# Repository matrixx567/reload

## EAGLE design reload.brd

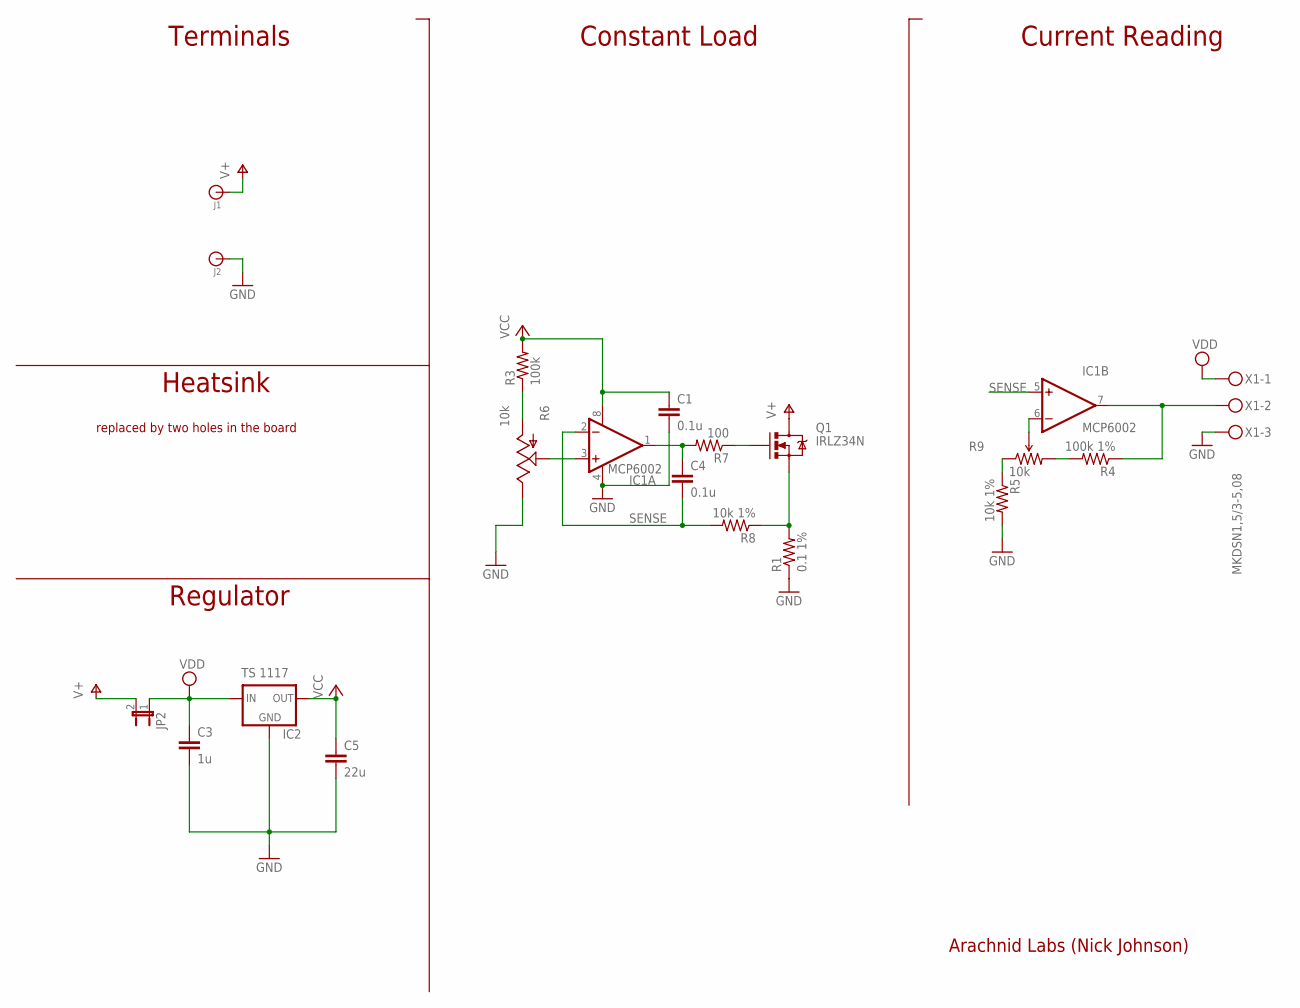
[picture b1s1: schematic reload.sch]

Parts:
C1, C4: 0.1u; 0805
C3: 1u; 0805
C5: 22u; 0805
IC1: MCP6002; SOP08
IC2: TS 1117; SOT223
J1, J2: BANANA_CONN
JP2: JUMPER-2PTH; 1X02
Q1: IRLZ34N; TO220V
R1: 0.1 1%; R2512
R3: 100k; 0805
R4: 100k 1%; 0805
R5, R8: 10k 1%; 0805
R6: 10k; ALPS_POT
R7: 100; 0805
R9: 10k; TRIMPOT-5MM
X1: MKDSN1,5/3-5,08

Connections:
GND: C1.2, C3.2, C5.2, IC1.4 (V-), IC2.2 (GND), J2.P$1, R1.1, R5.2, R6.P$1 (E), X1.3
IREF: IC1.7 (OUT), R4.1, X1.2
unnamed: C4.1, IC1.1 (OUT), R7.2
unnamed: R3.1, R6.P$3 (A)
unnamed: Q1.3 (S), R1.2, R8.1
unnamed: IC1.3 (+IN), R6.P$2 (S)
unnamed: IC1.6 (-IN), R9.B (WIPER)
unnamed: R5.1, R9.A (CCW)
unnamed: R4.2, R9.C (CW)
unnamed: Q1.1 (G), R7.1
SENSE: C4.2, IC1.2 (-IN), IC1.5 (+IN), R8.2
V+: J1.P$1, JP2.2, Q1.2 (D)
VCC: C1.1, C5.1, IC1.8 (V+), IC2.3 (OUT), R3.2
VDD: C3.1, IC2.1 (IN), JP2.1, X1.1

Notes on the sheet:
Terminals
Heatsink
Regulator
Constant Load
Current Reading
Arachnid Labs (Nick Johnson)
replaced by two holes in the board

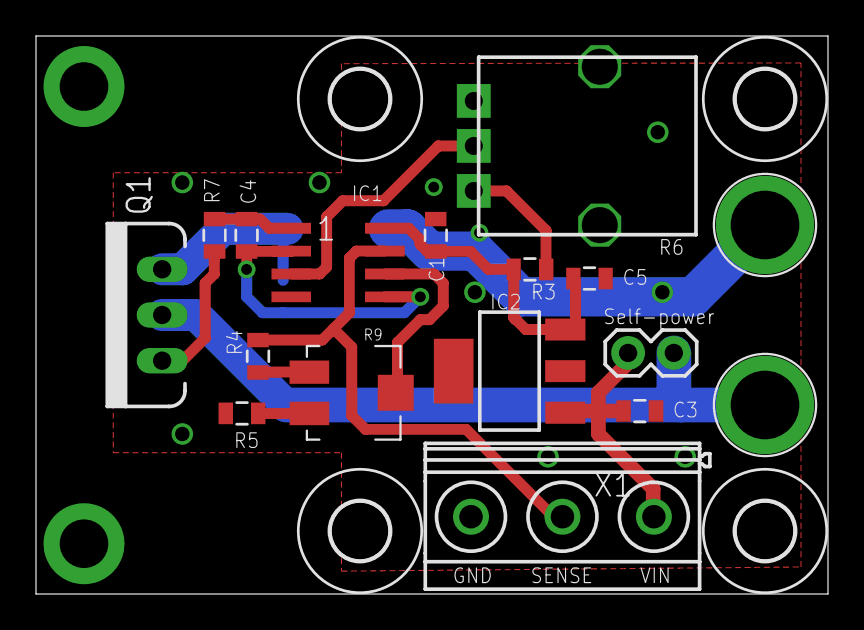
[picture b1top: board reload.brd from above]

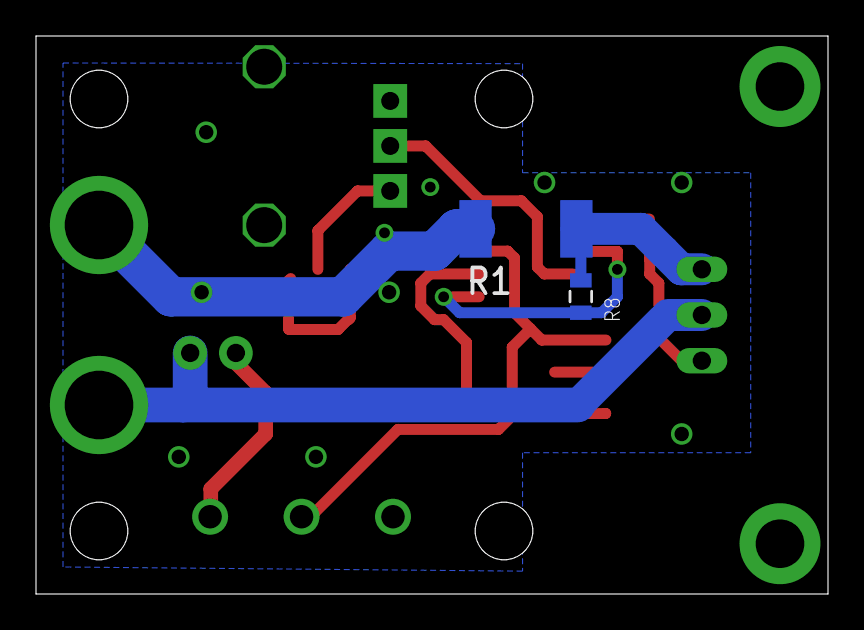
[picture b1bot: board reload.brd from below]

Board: 2 copper layers, 44.0 x 31.0 mm, 23 parts (2 on the bottom side), 14 nets.

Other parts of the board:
U$1, U$2, U$3, U$4: 3,2

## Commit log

2013-11-09 change components and layout
2015-07-10 change board layout
2015-08-26 change board text to vector types
2015-09-29 rearrange part identifiers for silkscreen change bottom ground plane
2015-09-29 add images for documentation
2015-10-11 improve for production

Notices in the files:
parts and their libraries:
SparkFun-Passives: Licensing: CC v3.0 Share-Alike You are welcome to use this library for commercial purposes.
SparkFun-Aesthetics: Released under the Creative Commons
SparkFun-Aesthetics: http://creativecommons.org/licenses/by-sa/3.0
